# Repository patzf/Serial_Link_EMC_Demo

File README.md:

# Serial_Link_EMC_Demo
Run common serial interfaces across different cables
<!-- ! [Preview of PCB](hw/rendering1.png)  -->

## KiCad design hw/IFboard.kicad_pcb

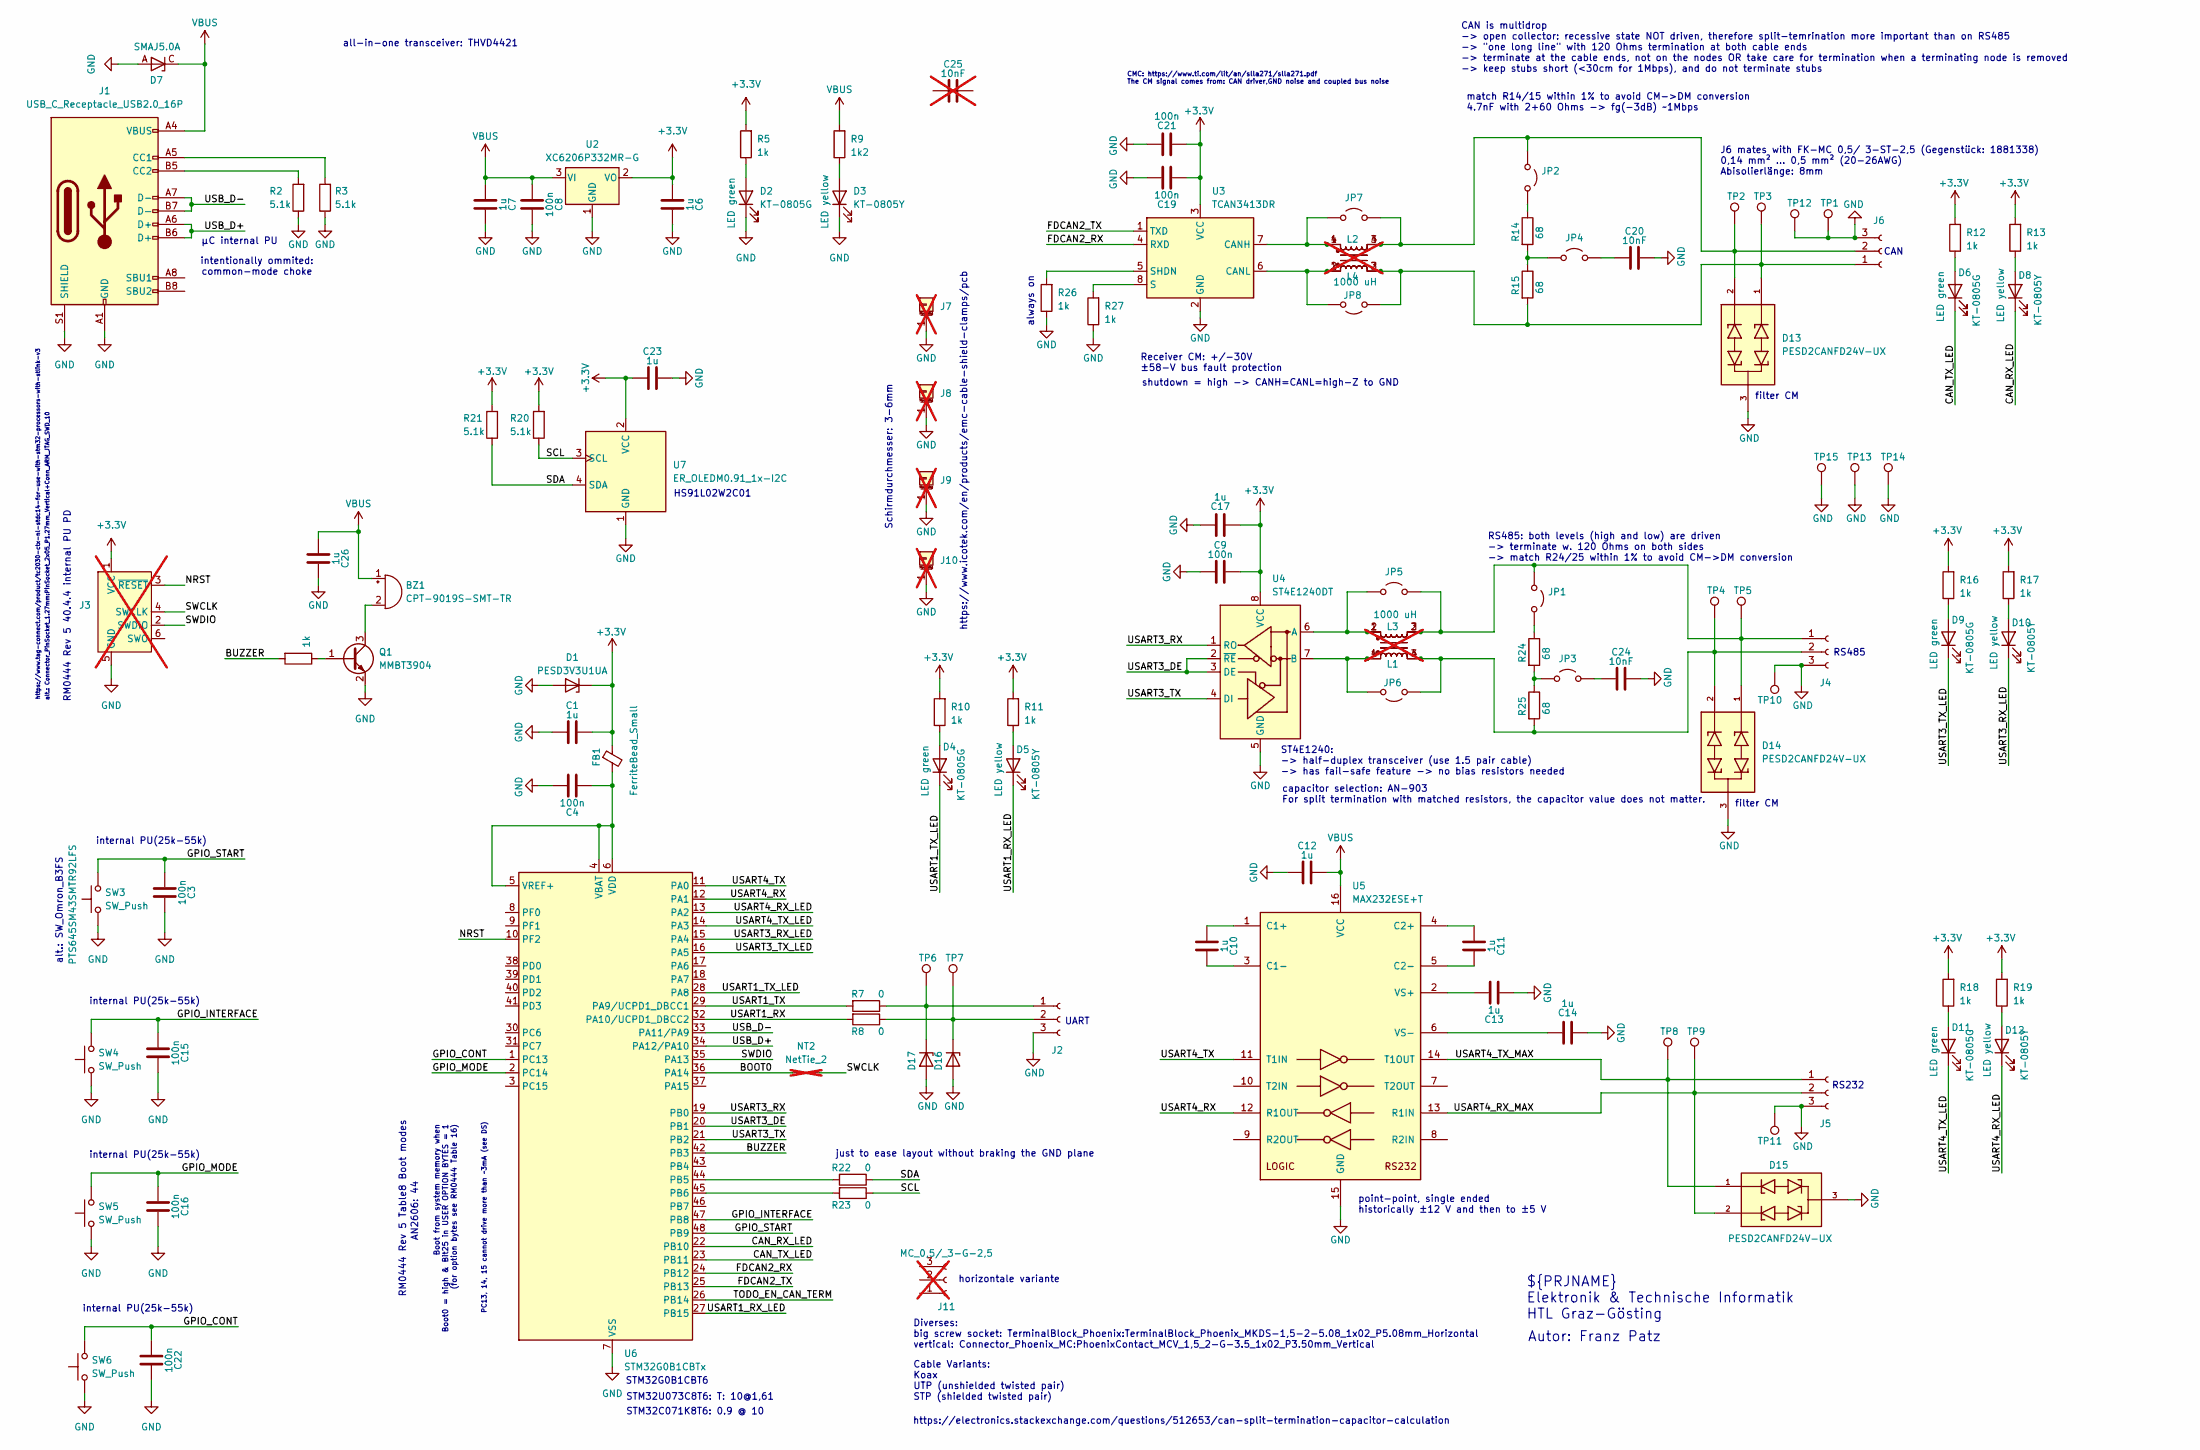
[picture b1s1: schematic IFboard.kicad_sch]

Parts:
BZ1: CPT-9019S-SMT-TR; Buzzer_CUI_CPT-9019S-SMT; LCSC Part # C95163
C1, C6, C7, C17, C23, C26: 1u; C_0402_1005Metric; LCSC Part # C52923
C3, C4, C8, C9, C15, C16, C19, C21, C22: 100n; C_0402_1005Metric; LCSC Part # C307331
C10, C11, C12, C13, C14: 1u; C_0603_1608Metric; LCSC Part # C15849
C20, C24: 10nF; C_0603_1608Metric; LCSC Part # C57112
C25: 10nF; C_0402_1005Metric; LCSC Part # C15195; not fitted
D1, D16, D17: PESD3V3U1UA; D_SOD-323; LCSC Part # C403915
D2, D4, D6, D9, D11: KT-0805G; LED_0805_2012Metric; LCSC Part # C2297
D3, D5, D8, D10, D12: KT-0805Y; LED_0805_2012Metric; LCSC Part # C2296
D7: SMAJ5.0A; D_SMA; LCSC Part # C2925443
D13, D14, D15: PESD2CANFD24V-UX; TVS_PESD2CANFD24V-UX; LCSC Part # C552487
FB1: FerriteBead_Small; R_0603_1608Metric; LCSC Part # C1002
J1: USB_C_Receptacle_USB2.0_16P; USB_C_Receptacle_HCTL_HC-TYPE-C-16P-01A; LCSC Part # C2894897
J2, J4, J5, J6: Phoenix_1881561; 1881561; LCSC Part # C3585554
J3: Conn_ARM_SWD_TagConnect_TC2030-NL; Tag-Connect_TC2030-IDC-NL_2x03_P1.27mm_Vertical; not fitted
J7, J8, J9, J10: IcoTec_36650.2; icotek 36650.2 PCB-4-V-6,8SKL 3-6; not fitted
J11: MC_0,5/_3-G-2,5; 1881451; not fitted
JP1, JP2, JP3, JP4, JP5, JP6, JP7, JP8: Jumper_2_Open; PinHeader_1x02_P2.54mm_Vertical; LCSC Part # C492401
L1, L2: 1000 uH; L_Wurth_WE-SL2-74422x; Part Number 744222; LCSC Part # C2651122; not fitted
L3, L4: 100 uH; L_Wurth_WE-CNSW-1812; LCSC Part # C2662370
NT2: NetTie_2; R_0402_1005Metric_solderjmp_short; not fitted
Q1: MMBT3904; SOT-23; LCSC Part # C7420353
R2, R3, R20, R21: 5.1k; R_0402_1005Metric; LCSC Part # C25905
R5, R10, R11, R12, R13, R16, R17, R18, R19, R26, R27, R29: 1k; R_0603_1608Metric; LCSC Part # C21190
R7, R8, R22, R23: 0; R_0603_1608Metric; LCSC Part # C21189
R9: 1k2; R_0603_1608Metric; LCSC Part # C22765
R14, R15, R24, R25: 68; R_0805_2012Metric; LCSC Part # C17802
SW3, SW4, SW5, SW6: SW_Push; SW_SPST_PTS645Sx43SMTR92; LCSC Part # C221880
TP1, TP10, TP11, TP12, TP13, TP14, TP15: TestPoint_Keystone_5019; TestPoint_Keystone_5019_Miniature; LCSC Part # C238131
TP2, TP3, TP4, TP5, TP6, TP7, TP8, TP9: TestPoint; TP_Keystone_5010-5014_Multipurpose; LCSC Part # C2906765
U2: XC6206P332MR-G; SOT-23-3; LCSC Part # C5446
U3: TCAN3413DR; SOIC-8_3.9x4.9mm_P1.27mm; LCSC Part # C22433320
U4: ST4E1240DT; SOIC-8_3.9x4.9mm_P1.27mm; LCSC Part # C29603430
U5: MAX232ESE+T; SOIC-16_3.9x9.9mm_P1.27mm; LCSC Part # C26860
U6: STM32G0B1CBTx; LQFP-48_7x7mm_P0.5mm; LCSC Part # C2847904
U7: ER_OLEDM0.91_1x-I2C; LCSC Part # C5248081

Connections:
+3.3V: C1.1, C6.2, C9.1, C17.2, C19.2, C21.2, C23.2, D1.1 (K), FB1.1, J3.1 (VCC), R5.2, R10.2, R11.2, R12.2, R13.2, R16.2, R17.2, R18.2, R19.2, R20.2, R21.2, U2.2 (VO), U3.3 (VCC), U4.8 (VCC), U7.2 (VCC)
/BOOT0: NT2.1, U6.36 (PA14)
/BUZZER: R29.2, U6.42 (PB3)
/CAN_RX_LED: D8.1 (K), U6.22 (PB10)
/CAN_TX_LED: D6.1 (K), U6.23 (PB11)
/FDCAN2_RX: U3.4 (RXD), U6.24 (PB12)
/FDCAN2_TX: U3.1 (TXD), U6.25 (PB13)
/GPIO_CONT: C22.2, SW6.2, U6.1 (PC13)
/GPIO_INTERFACE: C15.2, SW4.2, U6.47 (PB8)
/GPIO_MODE: C16.2, SW5.2, U6.2 (PC14)
/GPIO_START: C3.2, SW3.2, U6.48 (PB9)
/NRST: J3.3 (~RESET), U6.10 (PF2)
/SCL: R20.1, R23.1, U7.3 (SCL)
/SDA: R21.1, R22.1, U7.4 (SDA)
/SWCLK: J3.4 (SWCLK), NT2.2
/SWDIO: J3.2 (SWDIO), U6.35 (PA13)
/TODO_EN_CAN_TERM: U6.26 (PB14)
/USART1_RX: R8.2, U6.32 (PA10/UCPD1_DBCC2)
/USART1_RX_LED: D5.1 (K), U6.27 (PB15)
/USART1_TX: R7.2, U6.29 (PA9/UCPD1_DBCC1)
/USART1_TX_LED: D4.1 (K), U6.28 (PA8)
/USART3_DE: U4.2 (~RE), U4.3 (DE), U6.20 (PB1)
/USART3_RX: U4.1 (RO), U6.19 (PB0)
/USART3_RX_LED: D10.1 (K), U6.15 (PA4)
/USART3_TX: U4.4 (DI), U6.21 (PB2)
/USART3_TX_LED: D9.1 (K), U6.16 (PA5)
/USART4_RX: U5.12 (R1OUT), U6.12 (PA1)
/USART4_RX_LED: D12.1 (K), U6.13 (PA2)
/USART4_RX_MAX: D15.2, J5.2, TP9.1 (1_1), U5.13 (R1IN)
/USART4_TX: U5.11 (T1IN), U6.11 (PA0)
/USART4_TX_LED: D11.1 (K), U6.14 (PA3)
/USART4_TX_MAX: D15.1, J5.1, TP8.1 (1_1), U5.14 (T1OUT)
/USB_D+: J1.A6 (D+), J1.B6 (D+), U6.34 (PA12/PA10)
/USB_D-: J1.A7 (D-), J1.B7 (D-), U6.33 (PA11/PA9)
GND: C1.2, C3.1, C4.1, C6.1, C7.1, C8.1, C9.2, C12.2, C13.2, C14.2, C15.1, C16.1, C17.1, C19.1, C20.1, C21.1, C22.1, C23.1, C24.1, C26.1, D1.2 (A), D2.1 (K), D3.1 (K), D7.A, D13.3, D14.3, D15.3, D16.2 (A), D17.2 (A), J1.A1 (GND), J1.A12 (GND), J1.B1 (GND), J1.B12 (GND), J1.S1 (SHIELD), J2.3, J3.5 (GND), J4.3, J5.3, J6.3, J7.1 (MountPin_1), J8.1 (MountPin_1), J9.1 (MountPin_1), J10.1 (MountPin_1), Q1.2 (E), R2.1, R3.1, R26.1, R27.1, SW3.1, SW4.1, SW5.1, SW6.1, TP1.1 (1_1), TP10.1 (1_1), TP11.1 (1_1), TP12.1 (1_1), TP13.1 (1_1), TP14.1 (1_1), TP15.1 (1_1), U2.1 (GND), U3.2 (GND), U4.5 (GND), U5.15 (GND), U6.7 (VSS), U7.1 (GND)
unnamed: BZ1.2 (-), Q1.3 (C)
unnamed: D2.2 (A), R5.1
unnamed: D3.2 (A), R9.1
unnamed: D4.2 (A), R10.1
unnamed: D5.2 (A), R11.1
unnamed: D6.2 (A), R12.1
unnamed: D8.2 (A), R13.1
unnamed: D9.2 (A), R16.1
unnamed: D10.2 (A), R17.1
unnamed: D11.2 (A), R18.1
unnamed: D12.2 (A), R19.1
unnamed: D16.1 (K), J2.2, R8.1, TP7.1 (1_1)
unnamed: D17.1 (K), J2.1, R7.1, TP6.1 (1_1)
unnamed: J1.A5 (CC1), R3.2
unnamed: J1.B5 (CC2), R2.2
unnamed: D14.1, J4.1, JP1.1 (A), JP5.2 (B), L1.3, L3.2, TP5.1 (1_1)
unnamed: D14.2, J4.2, JP6.1 (A), L1.4, L3.3, R25.2, TP4.1 (1_1)
unnamed: D13.1, J6.1, JP8.1 (A), L2.3, L4.2, R15.2, TP3.1 (1_1)
unnamed: D13.2, J6.2, JP2.1 (A), JP7.2 (B), L2.4, L4.3, TP2.1 (1_1)
unnamed: JP1.2 (B), R24.1
unnamed: JP2.2 (B), R14.1
unnamed: JP3.1 (A), R24.2, R25.1
unnamed: C24.2, JP3.2 (B)
unnamed: JP4.1 (A), R14.2, R15.1
unnamed: C20.2, JP4.2 (B)
unnamed: JP5.1 (A), L1.2, L3.1, U4.6 (A)
unnamed: JP6.2 (B), L1.1, L3.4, U4.7 (B)
unnamed: JP7.1 (A), L2.1, L4.4, U3.7 (CANH)
unnamed: JP8.2 (B), L2.2, L4.1, U3.6 (CANL)
unnamed: Q1.1 (B), R29.1
unnamed: R27.2, U3.8 (S)
unnamed: R26.2, U3.5 (SHDN)
unnamed: C10.2, U5.1 (C1+)
unnamed: C10.1, U5.3 (C1-)
unnamed: C11.2, U5.4 (C2+)
unnamed: C11.1, U5.5 (C2-)
unnamed: C13.1, U5.2 (VS+)
unnamed: C14.1, U5.6 (VS-)
unnamed: R22.2, U6.44 (PB5)
unnamed: R23.2, U6.45 (PB6)
unnamed: C4.2, FB1.2, U6.4 (VBAT), U6.5 (VREF+), U6.6 (VDD)
VBUS: BZ1.1 (+), C7.2, C8.2, C12.1, C26.2, D7.C, J1.A4 (VBUS), J1.A9 (VBUS), J1.B4 (VBUS), J1.B9 (VBUS), R9.2, U2.3 (VI), U5.16 (VCC)

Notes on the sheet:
shutdown = high -> CANH=CANL=high-Z to GND
horizontale variante
RS485
alt.: Connector_PinSocket_1.27mm:PinSocket_2x05_P1.27mm_Vertical+Conn_ARM_JTAG_SWD_10
HS91L02W2C01
STM32U073C8T6: T: 10@1,61
capacitor selection: AN-903 For split termination with matched resistors, the capacitor value does not matter.
internal PU(25k-55k)
CMC: https://www.ti.com/lit/an/slla271/slla271.pdf The CM signal comes from: CAN driver,GND noise and coupled bus noise
Diverses: big screw socket: TerminalBlock_Phoenix:TerminalBlock_Phoenix_MKDS-1,5-2-5.08_1x02_P5.08mm_Horizontal vertical: Connector_Phoenix_MC:PhoenixContact_MCV_1,5_2-G-3.5_1x02_P3.50mm_Vertical
PC13, 14, 15 cannot drive more than ~3mA (see DS)
intentionally ommited: common-mode choke
J6 mates with FK-MC 0,5/ 3-ST-2,5 (Gegenstück: 1881338) 0,14 mm² ... 0,5 mm² (20-26AWG) Abisolierlänge: 8mm
CAN is multidrop -> open collector: recessive state NOT driven, therefore split-temrination more important than on RS485 -> "one long line" with 120 Ohms termination at both cable ends -> terminate at the cable ends, not on the nodes OR take care for termination when a terminating node is removed -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
filter CM
https://electronics.stackexchange.com/questions/512653/can-split-termination-capacitor-calculation
RM0444 Rev 5 40.4.4 internal PU PD
STM32G0B1CBT6
Boot from system memory when Boot0 = high & Bit25 in USER OPTION BYTES = 1 (for option bytes see RM0444 Table 16)
all-in-one transceiver: THVD4421
Schirmdurchmesser: 3-6mm
RS485: both levels (high and low) are driven -> terminate w. 120 Ohms on both sides -> match R24/25 within 1% to avoid CM->DM conversion
https://www.tag-connect.com/product/tc2030-ctx-nl-stdc14-for-use-with-stm32-processors-with-stlink-v3
STM32C071K8T6: 0.9 @ 10
µC internal PU
always on
RM0444 Rev 5 Table8 Boot modes
ST4E1240: -> half-duplex transceiver (use 1.5 pair cable) -> has fail-safe feature -> no bias resistors needed
UART
Autor: Franz Patz
alt.: SW_Omron_B3FS
Receiver CM: +/-30V ±58-V bus fault protection
CAN
Cable Variants: Koax UTP (unshielded twisted pair) STP (shielded twisted pair)
match R14/15 within 1% to avoid CM->DM conversion 4.7nF with 2+60 Ohms -> fg(-3dB) ~1Mbps
point-point, single ended historically ±12 V and then to ±5 V
AN2606: 44
RS232
${PRJNAME} Elektronik & Technische Informatik HTL Graz-Gösting
https://www.icotek.com/en/products/emc-cable-shield-clamps/pcb

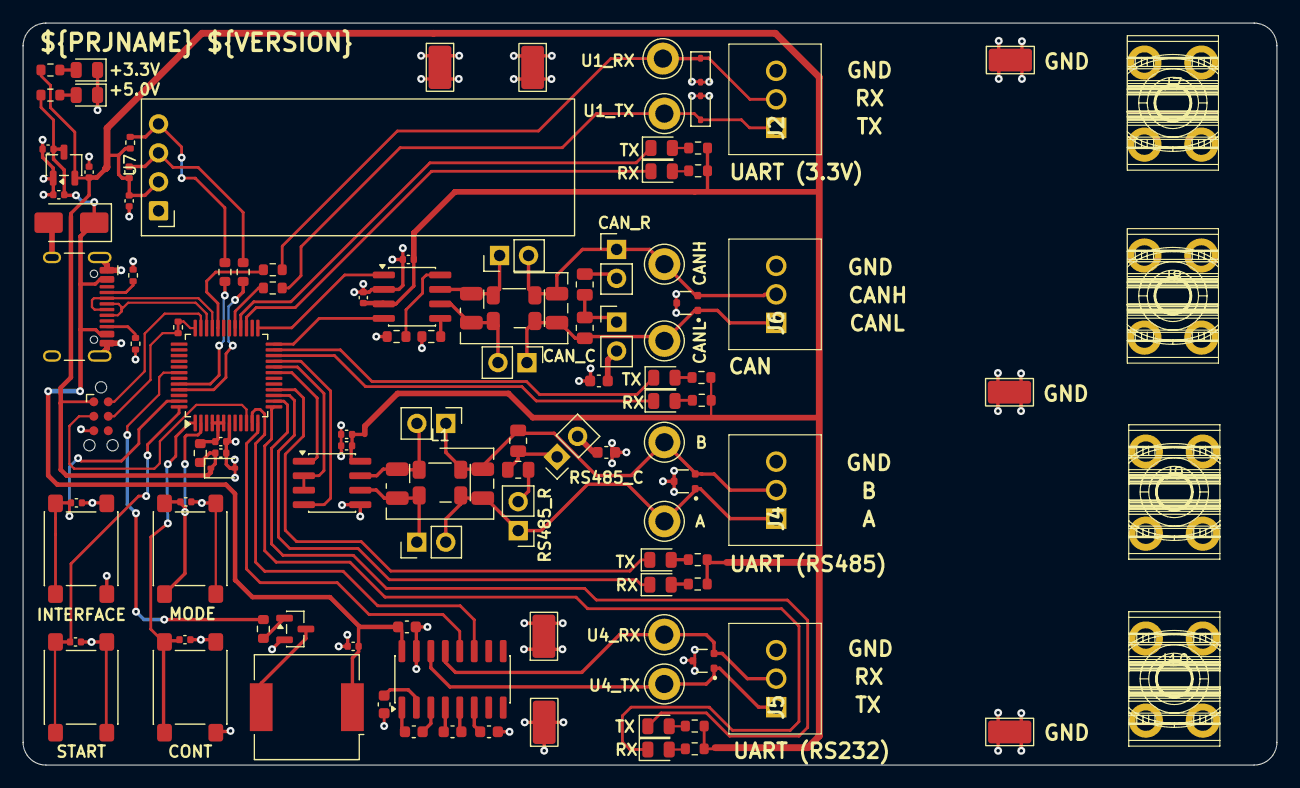
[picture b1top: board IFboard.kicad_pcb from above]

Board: 2 copper layers, 110.0 x 65.1 mm, 115 parts (0 on the bottom side), 76 nets.

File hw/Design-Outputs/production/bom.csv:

Designator,Footprint,Quantity,Value,LCSC Part #
BZ1,Buzzer_CUI_CPT-9019S-SMT,1,CPT-9019S-SMT-TR,C95163
"C1, C17, C23, C26, C6, C7",0402,6,1u,C52923
"C10, C11, C12, C13, C14",0603,5,1u,C15849
"C15, C16, C19, C21, C22, C3, C4, C8, C9",0402,9,100n,C307331
"C20, C24",0603,2,10nF,C57112
"D1, D16, D17",D_SOD-323,3,PESD3V3U1UA,C403915
"D10, D12, D3, D5, D8",0805,5,KT-0805Y,C2296
"D11, D2, D4, D6, D9",0805,5,KT-0805G,C2297
"D13, D14, D15",TVS_PESD2CANFD24V-UX,3,PESD2CANFD24V-UX,C552487
D7,D_SMA,1,SMAJ5.0A,C2925443
FB1,0603,1,FerriteBead_Small,C1002
J1,USB_C_Receptacle_HCTL_HC-TYPE-C-16P-01A,1,USB_C_Receptacle_USB2.0_16P,C2894897
"J2, J4, J5, J6",1881561,4,Phoenix_1881561,C3585554
"JP1, JP2, JP3, JP4, JP5, JP6, JP7, JP8",PinHeader_1x02_P2.54mm_Vertical,8,Jumper_2_Open,C492401
"L3, L4",L_Wurth_WE-CNSW-1812,2,100 uH,C2662370
Q1,SOT-23,1,MMBT3904,C7420353
"R10, R11, R12, R13, R16, R17, R18, R19, R26, R27, R29, R5",0603,12,1k,C21190
"R14, R15, R24, R25",0805,4,68,C17802
"R2, R20, R21, R3",0402,4,5.1k,C25905
"R22, R23, R7, R8",0603,4,0,C21189
R9,0603,1,1k2,C22765
"SW3, SW4, SW5, SW6",SW_SPST_PTS645Sx43SMTR92,4,SW_Push,C221880
"TP1, TP10, TP11, TP12, TP13, TP14, TP15",TestPoint_Keystone_5019_Miniature,7,TestPoint_Keystone_5019,C238131
"TP2, TP3, TP4, TP5, TP6, TP7, TP8, TP9",TP_Keystone_5010-5014_Multipurpose,8,TestPoint,C2906765
U2,SOT-23-3,1,XC6206P332MR-G,C5446
U3,SOIC-8_3.9x4.9mm_P1.27mm,1,TCAN3413DR,C22433320
U4,SOIC-8_3.9x4.9mm_P1.27mm,1,ST4E1240DT,C29603430
U5,SOIC-16_3.9x9.9mm_P1.27mm,1,MAX232ESE+T,C26860
U6,LQFP-48_7x7mm_P0.5mm,1,STM32G0B1CBTx,C2847904
U7,ER_OLEDM0.91_1x-I2C,1,ER_OLEDM0.91_1x-I2C,C5248081

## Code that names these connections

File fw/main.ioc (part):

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Mcu.Name=STM32G0B1C(B-C-E)Tx
Mcu.Package=LQFP48
Mcu.UserName=STM32G0B1CBTx
PA0.Mode=Asynchronous
PA0.Signal=USART4_TX
PA1.Mode=Asynchronous
PA1.Signal=USART4_RX
PA10.Mode=Asynchronous
PA10.Signal=USART1_RX
PA11\ [PA9].Mode=Device
PA11\ [PA9].Signal=USB_DM
PA12\ [PA10].Mode=Device
PA12\ [PA10].Signal=USB_DP
PA9.Mode=Asynchronous
PA9.Signal=USART1_TX
PB0.Mode=Asynchronous
PB0.Signal=USART3_RX
PB1.Mode=Hardware Flow Control (RS485)
PB1.Signal=USART3_DE
PB12.Mode=FDCAN_Activate
PB12.Signal=FDCAN2_RX
PB13.Mode=FDCAN_Activate
PB13.Signal=FDCAN2_TX
PB2.Mode=Asynchronous
PB2.Signal=USART3_TX
PB5.GPIOParameters=GPIO_Label
PB5.GPIO_Label=DONOTUSE
PB5.Signal=GPIO_Input
PB6.Mode=I2C
PB6.Signal=I2C1_SCL
PB7.Mode=I2C
PB7.Signal=I2C1_SDA
PB8.GPIOParameters=GPIO_PuPd,GPIO_Label,GPIO_ModeDefaultEXTI
PB8.GPIO_Label=INTERFACE
PB8.GPIO_ModeDefaultEXTI=GPIO_MODE_IT_RISING_FALLING
PB8.GPIO_PuPd=GPIO_PULLUP
PB8.Signal=GPXTI8
PB9.GPIOParameters=GPIO_PuPd,GPIO_Label,GPIO_ModeDefaultEXTI
PB9.GPIO_Label=START
PB9.GPIO_ModeDefaultEXTI=GPIO_MODE_IT_RISING_FALLING
PB9.GPIO_PuPd=GPIO_PULLUP
PB9.Signal=GPXTI9
PC13.GPIOParameters=GPIO_PuPd,GPIO_Label,GPIO_ModeDefaultEXTI
PC13.GPIO_Label=CONT
PC13.GPIO_ModeDefaultEXTI=GPIO_MODE_IT_RISING_FALLING
PC13.GPIO_PuPd=GPIO_PULLUP
PC13.Signal=GPXTI13
PC14-OSC32_IN\ (PC14).GPIOParameters=GPIO_PuPd,GPIO_Label,GPIO_ModeDefaultEXTI
PC14-OSC32_IN\ (PC14).GPIO_Label=MODE
PC14-OSC32_IN\ (PC14).GPIO_ModeDefaultEXTI=GPIO_MODE_IT_RISING_FALLING
PC14-OSC32_IN\ (PC14).GPIO_PuPd=GPIO_PULLUP
PC14-OSC32_IN\ (PC14).Signal=GPXTI14
RCC.HSE_VALUE=8000000
RCC.SYSCLKFreq_VALUE=64000000
RCC.SYSCLKSource=RCC_SYSCLKSOURCE_PLLCLK
board=custom

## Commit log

2026-05-09 copied all parts into personal lib to have JLC numbers added per default
2026-05-09 add preview rendering to README.md
2026-05-09 fix readme
2026-05-10 wip:add small display
2026-05-11 add simple ssd1306 test
2026-05-11 add reference to ssd1306 libary
2026-05-11 wip: initial comms logic
2026-05-11 display I2C connection done. not proud of it =)
2026-05-12 cleanup
2026-05-12 move jobset to root dir
2026-05-13 forgot last time
2026-05-13 tag:3.5mm connectors
2026-05-14 swapped poition of two connectors for better routing
2026-05-15 added CMCs to RS485 and CAN interfaces
2026-05-16 changed position of SMSs and added TVS diodes to RS485 and CAN
2026-05-16 wip:testpoints
2026-05-20 added jumper to add/remove split-termination capacitors
2026-05-26 train session
2026-05-27 updated rendering
2026-05-28 modified connectors to vertical
2026-05-29 moving pdfs to ds directory
2026-06-01 added jumpers to be able to short CMCs
2026-06-02 corrected rotation offsets for JLC
2026-06-03 test ibom
2026-06-03 moved ibom to Design-Outputs directory
2026-06-04 first version sent to JLC
2026-06-05 modified gitignore to keep csv production data under Version control
2026-06-18 merged display code - display functional after fixing error in HW (SDA must go to PB7 instead of PB5)
2026-06-19 few lines hacked so a counter is shown on the display when sending data over UART1 to check basic TX/RX functionality
